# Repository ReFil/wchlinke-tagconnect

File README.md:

# wchlinke-tagconnect
 WCHlinkE to Tag Connect 6 pin adapter

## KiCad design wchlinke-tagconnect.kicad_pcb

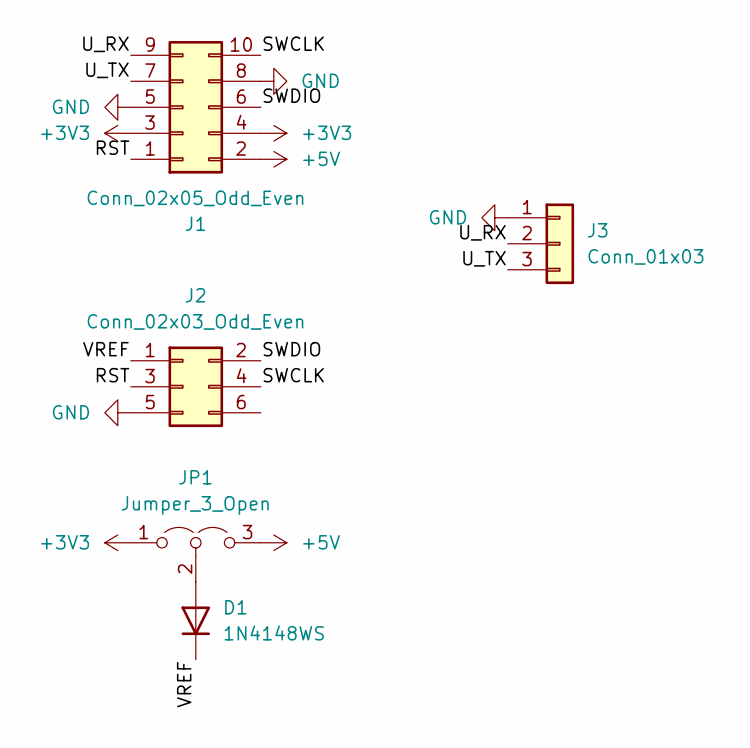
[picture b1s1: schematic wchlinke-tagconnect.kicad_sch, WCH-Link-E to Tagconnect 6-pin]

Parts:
D1: 1N4148WS; D_SOD-323
J1: Conn_02x05_Odd_Even; IDC-Header_2x05_P2.54mm_Horizontal
J2: Conn_02x03_Odd_Even; IDC-Header_2x03_P2.54mm_Vertical
J3: Conn_01x03; PinHeader_1x03_P2.54mm_Vertical
JP1: Jumper_3_Open; PinHeader_1x03_P2.54mm_Vertical

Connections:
+3V3: J1.3, J1.4, JP1.1 (A)
+5V: J1.2, JP1.3 (B)
/RST: J1.1, J2.3
/SWCLK: J1.10, J2.4
/SWDIO: J1.6, J2.2
/U_RX: J1.9, J3.2
/U_TX: J1.7, J3.3
/VREF: D1.1 (K), J2.1
GND: J1.5, J1.8, J2.5, J3.1
unnamed: D1.2 (A), JP1.2 (C)

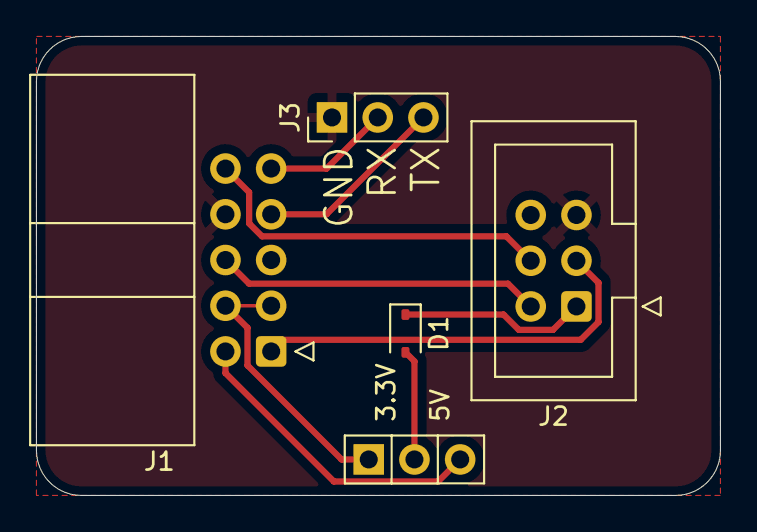
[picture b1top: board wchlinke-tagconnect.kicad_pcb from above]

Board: 2 copper layers, 38.0 x 25.5 mm, 5 parts (0 on the bottom side), 10 nets.

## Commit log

2025-01-24 Commit Gerbers
